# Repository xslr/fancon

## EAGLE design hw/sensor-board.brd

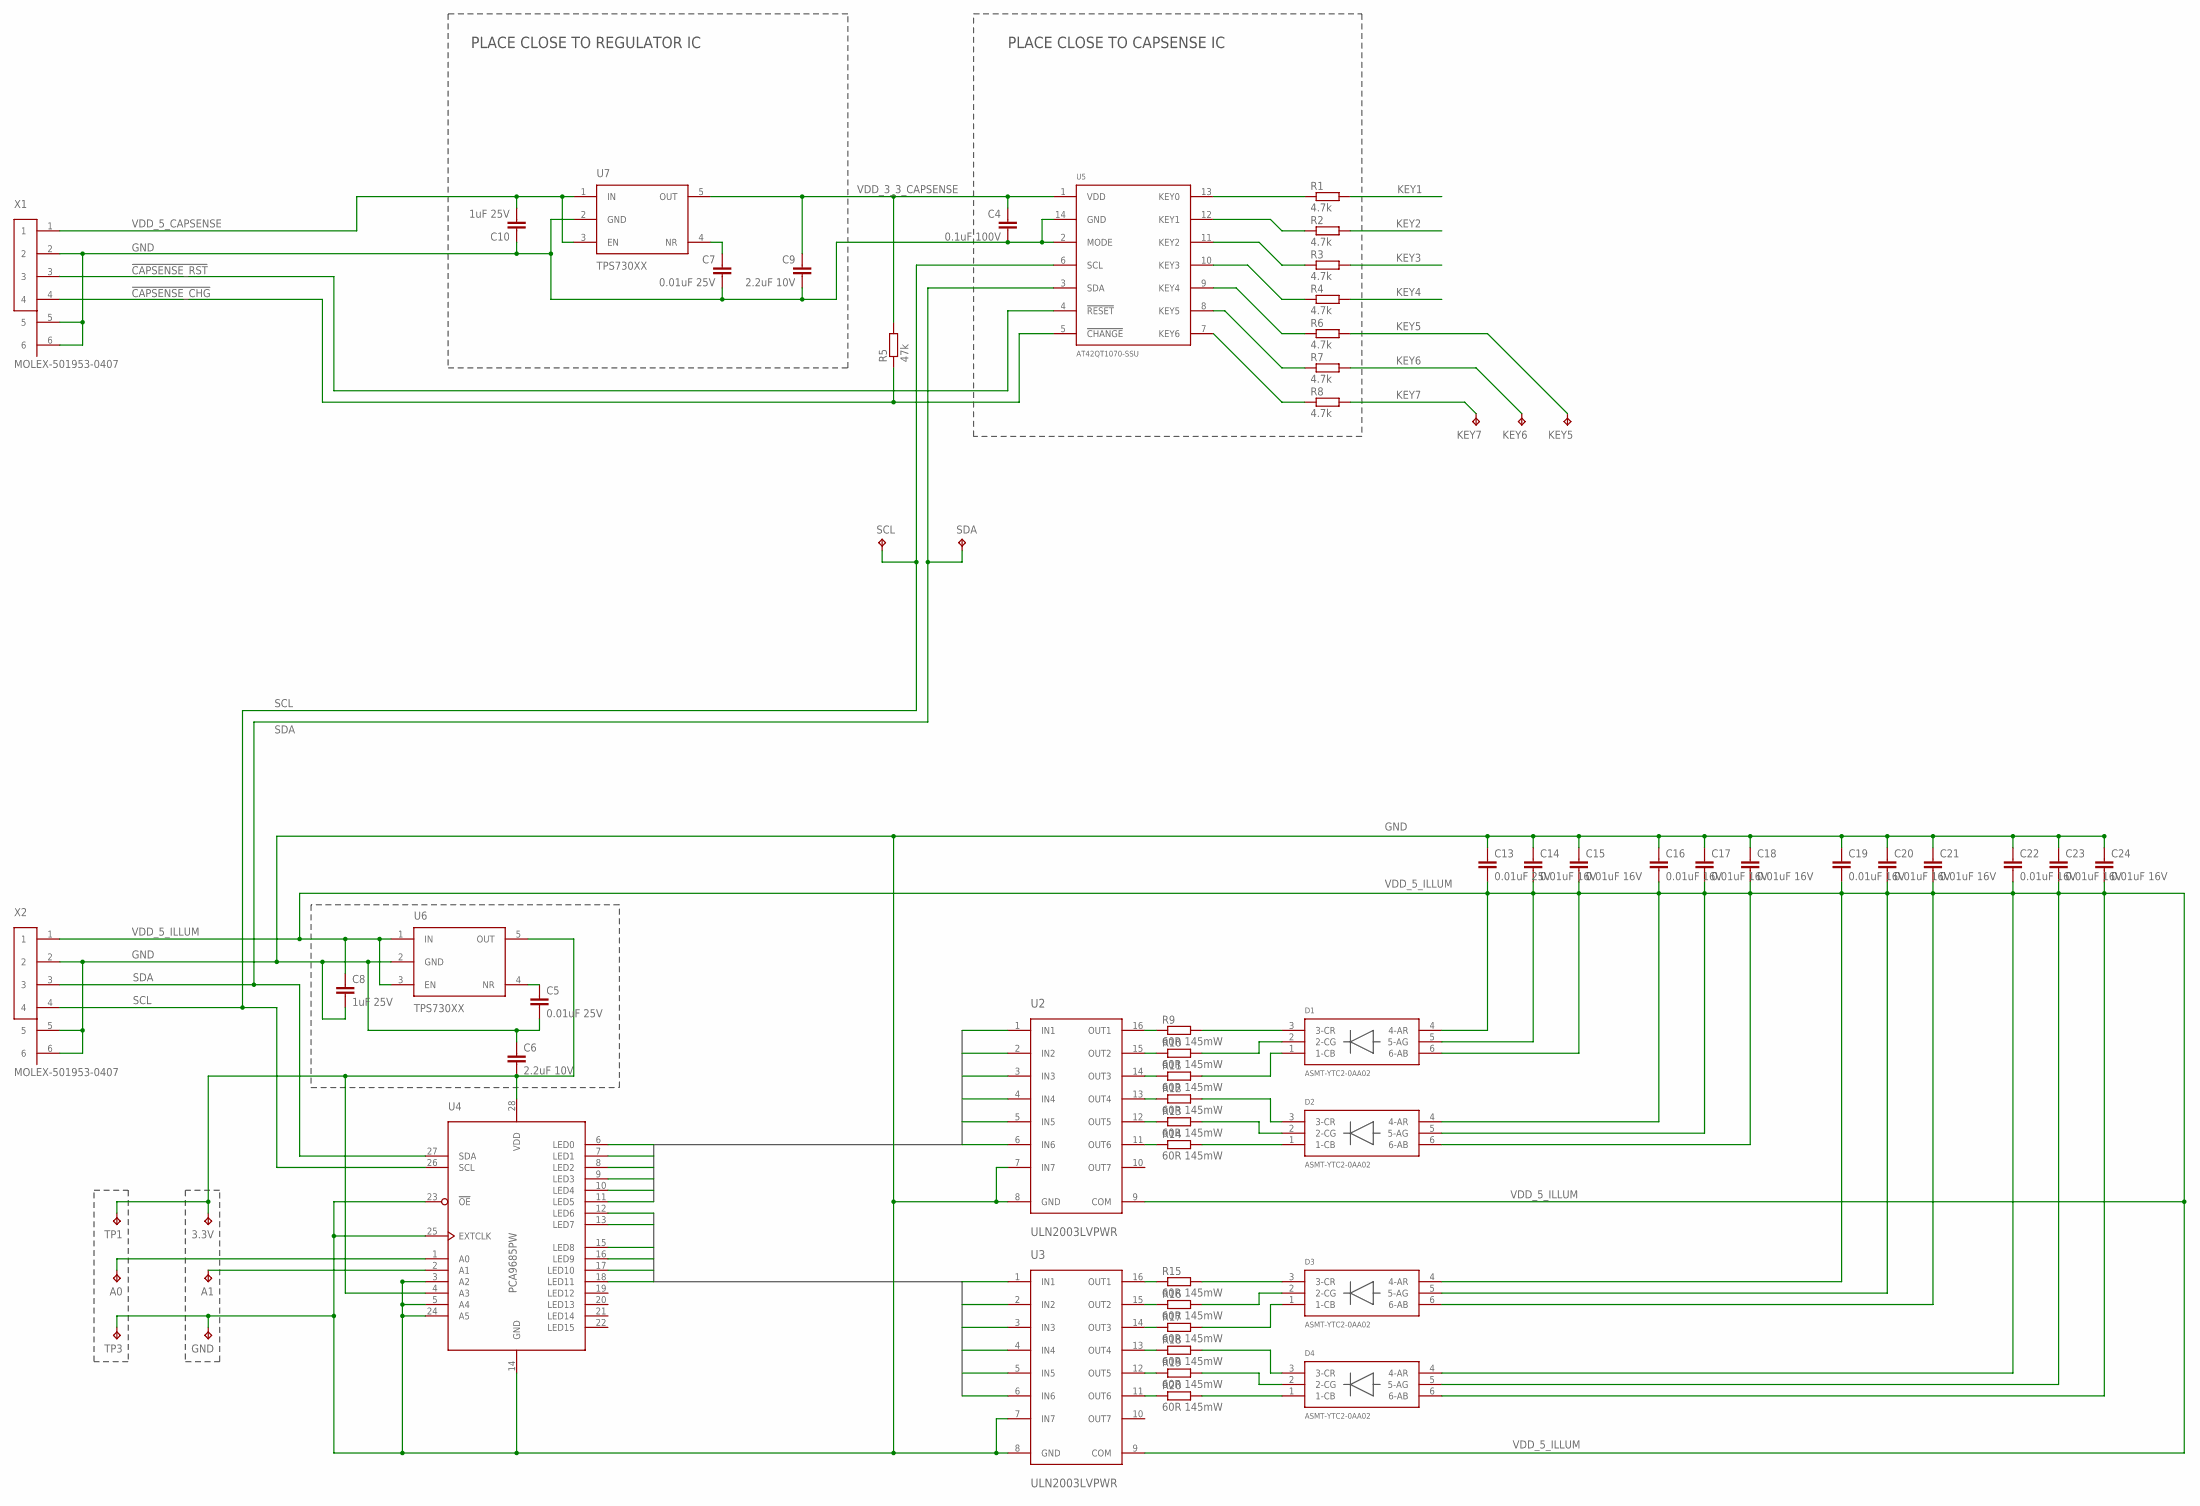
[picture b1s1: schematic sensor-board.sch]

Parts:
3.3V: TPB1,27; B1,27
A0, A1: TPB1,27; B1,27
C4: 0.1uF 100V; C0402K; MFR_PART 0402YC104KAT2A
C5, C7, C13: 0.01uF 25V; C0402K; MFR_PART C0402C103J3RACTU
C6: 2.2uF 10V; C0402K; MFR_PART C0402C225M8PAC TU
C8, C10: 1uF 25V; C0402K; MFR_PART C1005X5R1A105K050BB
C9: 2.2uF 10V; C0402K; MFR_PART C1608X7R1C105K080AC
C14, C15, C16, C17, C18, C19, C20, C21, C22, C23, C24: 0.01uF 16V; C0402K; MFR_PART C0402C103J3RACTU
D1, D2, D3, D4: ASMT-YTC2-0AA02; ASMT-YTC2-0AA02-REV
GND: TPB1,27; B1,27
KEY5, KEY6, KEY7: TPTP06R; TP06R
R1, R2, R3, R4, R6, R7, R8: 4.7k; R0402; MFR_PART PCF0402PR-4K7BT1
R5: 47k; R0402; MFR_PART RC0402JR-0747KL
R9, R10, R11, R12, R13, R14, R15, R16, R17, R18, R19, R20: 60R 145mW; R0603; MFR_PART ERJP03F62R0V
SCL: TPTP06R; TP06R
SDA: TPTP06R; TP06R
TP1, TP3: TPB1,27; B1,27
U2, U3: ULN2003LVPWR; TSSOP-PW-R-PDSO-G16
U4: PCA9685PW; SOT361-1
U5: AT42QT1070-SSU; SO14
U6, U7: TPS730XX; SOT23-5
X1, X2: MOLEX-501953-0407

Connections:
!CAPSENSE_CHG!: R5.1, U5.5 (!CHANGE!), X1.4
!CAPSENSE_RST!: U5.4 (!RESET!), X1.3
GND: C4.2, C5.2, C6.1, C7.2, C8.2, C9.2, C10.1, C13.1, C14.1, C15.1, C16.1, C17.1, C18.1, C19.1, C20.1, C21.1, C22.1, C23.1, C24.1, GND.TP, TP3.TP, U2.7 (IN7), U2.8 (GND), U3.7 (IN7), U3.8 (GND), U4.3 (A2), U4.5 (A4), U4.14 (GND), U4.23 (!OE!), U4.24 (A5), U4.25 (EXTCLK), U5.2 (MODE), U5.14 (GND), U6.2 (GND), U7.2 (GND), X1.2, X1.5, X1.6, X2.2, X2.5, X2.6
KEY1: R1.2
KEY2: R2.2
KEY3: R3.2
KEY4: R4.2
KEY5: KEY5.TP, R6.2
KEY6: KEY6.TP, R7.2
KEY7: KEY7.TP, R8.2
LEDOUT_A1: U2.1 (IN1), U4.6 (LED0)
LEDOUT_A2: U2.2 (IN2), U4.7 (LED1)
LEDOUT_A3: U2.3 (IN3), U4.8 (LED2)
LEDOUT_A4: U2.4 (IN4), U4.9 (LED3)
LEDOUT_A5: U2.5 (IN5), U4.10 (LED4)
LEDOUT_A6: U2.6 (IN6), U4.11 (LED5)
LEDOUT_B1: U3.1 (IN1), U4.12 (LED6)
LEDOUT_B2: U3.2 (IN2), U4.13 (LED7)
LEDOUT_B3: U3.3 (IN3), U4.15 (LED8)
LEDOUT_B4: U3.4 (IN4), U4.16 (LED9)
LEDOUT_B5: U3.5 (IN5), U4.17 (LED10)
LEDOUT_B6: U3.6 (IN6), U4.18 (LED11)
unnamed: C5.1, U6.4 (NR)
unnamed: A0.TP, U4.1 (A0)
unnamed: A1.TP, U4.2 (A1)
unnamed: C7.1, U7.4 (NR)
unnamed: R6.1, U5.9 (KEY4)
unnamed: R7.1, U5.8 (KEY5)
unnamed: R8.1, U5.7 (KEY6)
unnamed: R1.1, U5.13 (KEY0)
unnamed: R2.1, U5.12 (KEY1)
unnamed: R3.1, U5.11 (KEY2)
unnamed: R4.1, U5.10 (KEY3)
unnamed: D4.1 (1-CB), R20.2
unnamed: D1.1 (1-CB), R11.2
unnamed: D1.2 (2-CG), R10.2
unnamed: D3.3 (3-CR), R15.2
unnamed: D2.3 (3-CR), R12.2
unnamed: D2.2 (2-CG), R13.2
unnamed: R15.1, U3.16 (OUT1)
unnamed: R16.1, U3.15 (OUT2)
unnamed: D3.1 (1-CB), R17.2
unnamed: D3.2 (2-CG), R16.2
unnamed: D4.3 (3-CR), R18.2
unnamed: D4.2 (2-CG), R19.2
unnamed: R17.1, U3.14 (OUT3)
unnamed: R18.1, U3.13 (OUT4)
unnamed: R19.1, U3.12 (OUT5)
unnamed: R20.1, U3.11 (OUT6)
unnamed: D2.1 (1-CB), R14.2
unnamed: D1.3 (3-CR), R9.2
unnamed: R9.1, U2.16 (OUT1)
unnamed: R10.1, U2.15 (OUT2)
unnamed: R11.1, U2.14 (OUT3)
unnamed: R12.1, U2.13 (OUT4)
unnamed: R13.1, U2.12 (OUT5)
unnamed: R14.1, U2.11 (OUT6)
SCL: SCL.TP, U4.26 (SCL), U5.6 (SCL), X2.4
SDA: SDA.TP, U4.27 (SDA), U5.3 (SDA), X2.3
VDD_3_3_CAPSENSE: C4.1, C9.1, R5.2, U5.1 (VDD), U7.5 (OUT)
VDD_3_3_PWMDRIVE: 3.3V.TP, C6.2, TP1.TP, U4.4 (A3), U4.28 (VDD), U6.5 (OUT)
VDD_5_CAPSENSE: C10.2, U7.1 (IN), U7.3 (EN), X1.1
VDD_5_ILLUM: C8.1, C13.2, C14.2, C15.2, C16.2, C17.2, C18.2, C19.2, C20.2, C21.2, C22.2, C23.2, C24.2, D1.4 (4-AR), D1.5 (5-AG), D1.6 (6-AB), D2.4 (4-AR), D2.5 (5-AG), D2.6 (6-AB), D3.4 (4-AR), D3.5 (5-AG), D3.6 (6-AB), D4.4 (4-AR), D4.5 (5-AG), D4.6 (6-AB), U2.9 (COM), U3.9 (COM), U6.1 (IN), U6.3 (EN), X2.1

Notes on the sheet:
PLACE CLOSE TO CAPSENSE IC
PLACE CLOSE TO REGULATOR IC

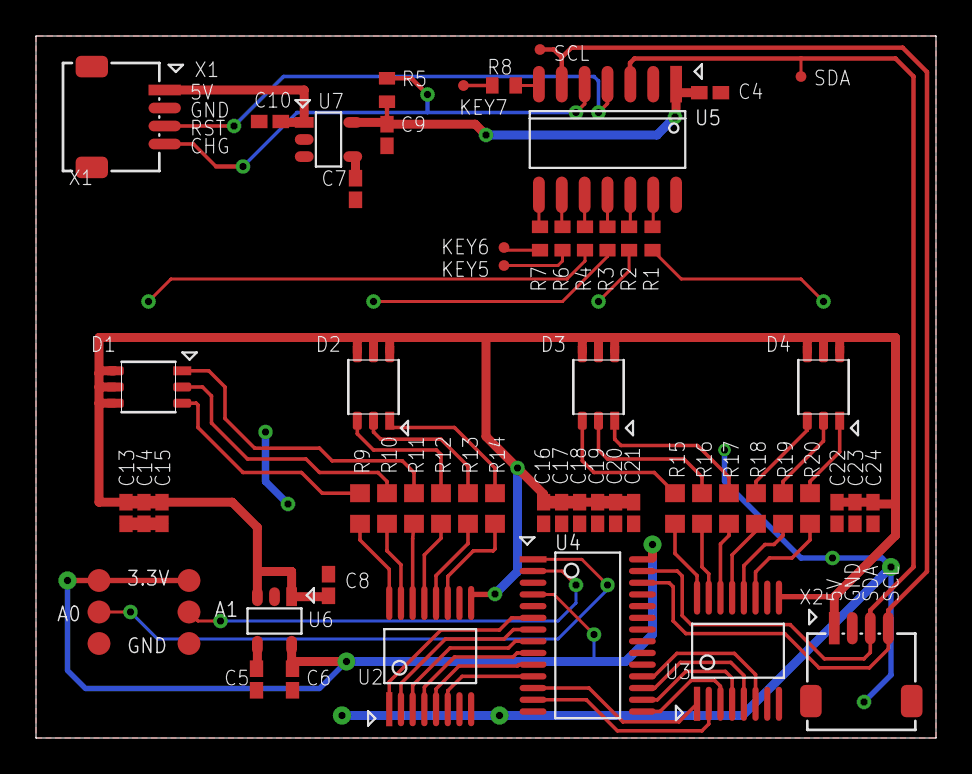
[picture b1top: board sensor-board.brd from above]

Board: 4 copper layers, 50.0 x 39.0 mm, 62 parts (0 on the bottom side), 59 nets.

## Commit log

2013-06-09 Initial import.
2013-06-09 Add readme.
2013-06-09 Update readme.
2013-06-09 Update LED driver package for easier hand soldering.
    New land patterns for PCA9685PW and ULN2003LV hae 0.5 mm of pads
    extending past the IC pins to allow the soldering iron to make contact
    with the pad.
2013-06-09 Update VREG and connectors for solderability.
2013-06-10 Connect capsense controller/buttons/B2B connector.
2013-06-11 Partly complete layout.
    Pending schematic tasks:
    1. Replace 10 pin sensor board to main board connector with a higher
    pin count variant for unrouted signals on LED controller and
    RST,CHANGE pins on touch controller.
    2. Add pull ups on control and comm lines of touch and led ICs,
    as needed.
2013-06-12 Compact the layout of LED driving circuitry.
    Additional space has been created for a larger sensor to main board
    connector.
2013-06-15 Change capsense IC to QT1070. Routing finished.
    Schematic and routing need to be checked against LED and CAPSENSE IC
    datasheets wrt operational requirements.
2013-06-16 Increase polygon wire width from 0 to 0.16
2013-06-16 Fix sourcing info for components.
2013-06-17 Create option to share LDO between sensor boards.
    This is done to reduce the BOM. If necessary, the voltage regulator can
    be installed later on as the land pattern stays.
    Label connector signals.
    Adjust some silkscreen positions.
2013-06-18 Add pullup to capsense change line.
    Capsense schematic and layout checked wrt datasheet.
2013-06-20 Switched VDD of LED PWM driver to 3.3V.
    Added an LDO to generate VDD for LED PWM driver.
2013-06-20 Round pads of LDO for LED driver.
2013-06-22 Update part number and values for LDO caps.
    Optimize cap placement near LDOs.
2013-06-23 Route unused sensing lines to test points.
    Resolve DRC issues due to silkscreen over stop mask.
2013-07-02 Sync part names for LED caps and resistors.
    Label power supply nets.
2013-07-03 Reduce fpanel PCB height to 39mm.
    This reduction in height will help fit the pcb into standard 5.25" bays.
2013-07-03 Move SCL and SDA lines closer to inside.
    This is done to improve manufacturing reliability.
